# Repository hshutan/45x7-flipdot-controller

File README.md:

**This project is old! I do not recommend my hardware based project anymore, check out my RS-485 protocol-based projects! [Main Flipdot Project Page Here](https://github.com/hshutan/FlipDotCompendium)**

---

# 45x7-flipdot-controller
Custom PCB controller board for a single 45x7 flip dot panel from a Luminator MAX3000 SideSign

# How To

**A much more [detailed How To](#detailed) is below**

You will need the following items to assemble a flip dot sign using my PCB

1. The PCB in this github project which can be ordered from [OSH Park](https://oshpark.com/shared_projects/JROcn5LK) or another fab.
2. [My simple Arduino clock program](https://github.com/hshutan/FlipDotDisplay_Clock1_SWv1) which contains my `Matrix_CoProcessor` library, a library specifically built to drive this PCB.
3. Surface mount silicon parts: see the [Digi-Key BOM file](https://github.com/hshutan/45x7-flipdot-controller/blob/master/FlipDotBOM.csv)
  - Note that the Digi-Key BOM does not include the two through hole capacitors you will need.
4. A Luminator MAX3000 Side Sign.
  - I purchased mine from [Rollsign Gallery](http://rollsigngallery.com/). A single Luminator MAX3000 side sign will have two 45x7 display panels inside, which are very easy to remove.
5. A microcontroller or Arduino, and various power supply components to provide the different needed voltages.
  - I like Paul Stoffregen's Arduino compatible [Teensy](http://www.pjrc.com/) but often use [Arduino Pro Mini](https://www.arduino.cc/en/Main/ArduinoBoardProMini) clones from eBay for less demanding projects.

# Notes
The silkscreen for the 64 pin connector is for aesthetics. You should install the connector on the back of the board not the front, using the silkscreen for orientation reference only.

There are three voltages: Logic (5v), Flip (12-15v), LED (19v or 400mA max)

HW Rev1 of the PCB does not include any current limiting for the flip dots, or for the LEDs. I am using a 60mA current limiter in-line with the flip dot voltage line. The dots seem to flip best based on voltage and not current, which is why I am using such a small current. The LEDs are meant to be driven at 19 volts max, however less is safer. A current limit of 350mA would be safe for the LEDs.

My first prototype clock/sign with this PCB uses 15 volts for both the LEDs and flip dots. This means the LEDs are always on, although not near their maximum brightness. I am using a 5 volt Arduino Pro Mini, and also supplying 5 volts to the logic voltage input on the PCB.

Watch for ground loops, as I believe these cause weak/un-reliable flips. Because the grounds are all "commoned" on the PCB, do not tie any of your grounds together pre-PCB.

Luminator and MAX3000 are trade names of the Luminator Technology Group, not mine.

# Detailed How To / Step by Step Instructions
1. Acquire a Luminator MAX3000 Side Sign. I found mine on [Rollsign Gallery](http://rollsigngallery.com/).
  - A single Luminator side sign will contain two 45x7 panels.
2. Order the PCB in this github project, it can be ordered with a few clicks from [OSH Park](https://oshpark.com/shared_projects/JROcn5LK)
3. Order the bill of materials ([see CSV file](https://github.com/hshutan/45x7-flipdot-controller/blob/master/FlipDotBOM.csv))
  - Also grab two spare through hole capacitors from your parts bin. Try a 50 volt 330 microfarad for the flip voltage, and a 16 volt 100 microfarad capacitor for the logic voltage.
4. Take apart the MAX3000 side sign and remove both of the 45x7 panels.
5. Assemble the PCB by placing all components and soldering. Hot air can be used for all the surface mount components.
  - For aesthetics, the PCB has very little silk screen. Here is how to place components: Pin 1 of each IC is in the lower left of the land pattern when viewing the board from the top (see PCB pictures at the top of this page).
  - The 0805 (2012 Metric) pads in the lower right area of the PCB are for the pull-up and pull-down resistors.
  - The 0805 (2012 Metric) pads in the upper left of the PCB are for the 0.1 microfarad shift register supporting capacitors.
6. Program an Arduino or microcontroller with the [test pattern](https://github.com/hshutan/FlipDotDisplay_TestPatterns_SWv1) software. A good test pattern to start with is `testPattern2()`
7. Hook up the Arduino per the comments in the code:
  - Arduino Uno pin 11, to SER on PCB
  - Arduino Uno pin 13, to SCK on PCB
  - Arduino Uno pin 10, to RCK on PCB
  - Arduino 5v, to 5v+ on PCB
8. Connect a power supply (start with 10-12 volts) to GND and Flip+ on the PCB.
  - For prototyping, use a constant voltage/constant current power supply. This will allow you to limit the current to 100mA (or less) for safety, and also to test flip reliability at different voltages. If you are using my `Matrix_CoProcessor` library that comes with the [test pattern](https://github.com/hshutan/FlipDotDisplay_TestPatterns_SWv1) software, then there is little risk of a flip dot being energized for more than a few hundred microseconds, however you should still use current limiting of 100mA or less to prevent damage if any paths remain energized for too long.

# Thanks
I would like to thank the following sources:
- [Dottie the Flip Dot Clock](http://dhenshaw.com/Art/Dottie/start.html)
- [Rollsign Gallery](http://rollsigngallery.com/)

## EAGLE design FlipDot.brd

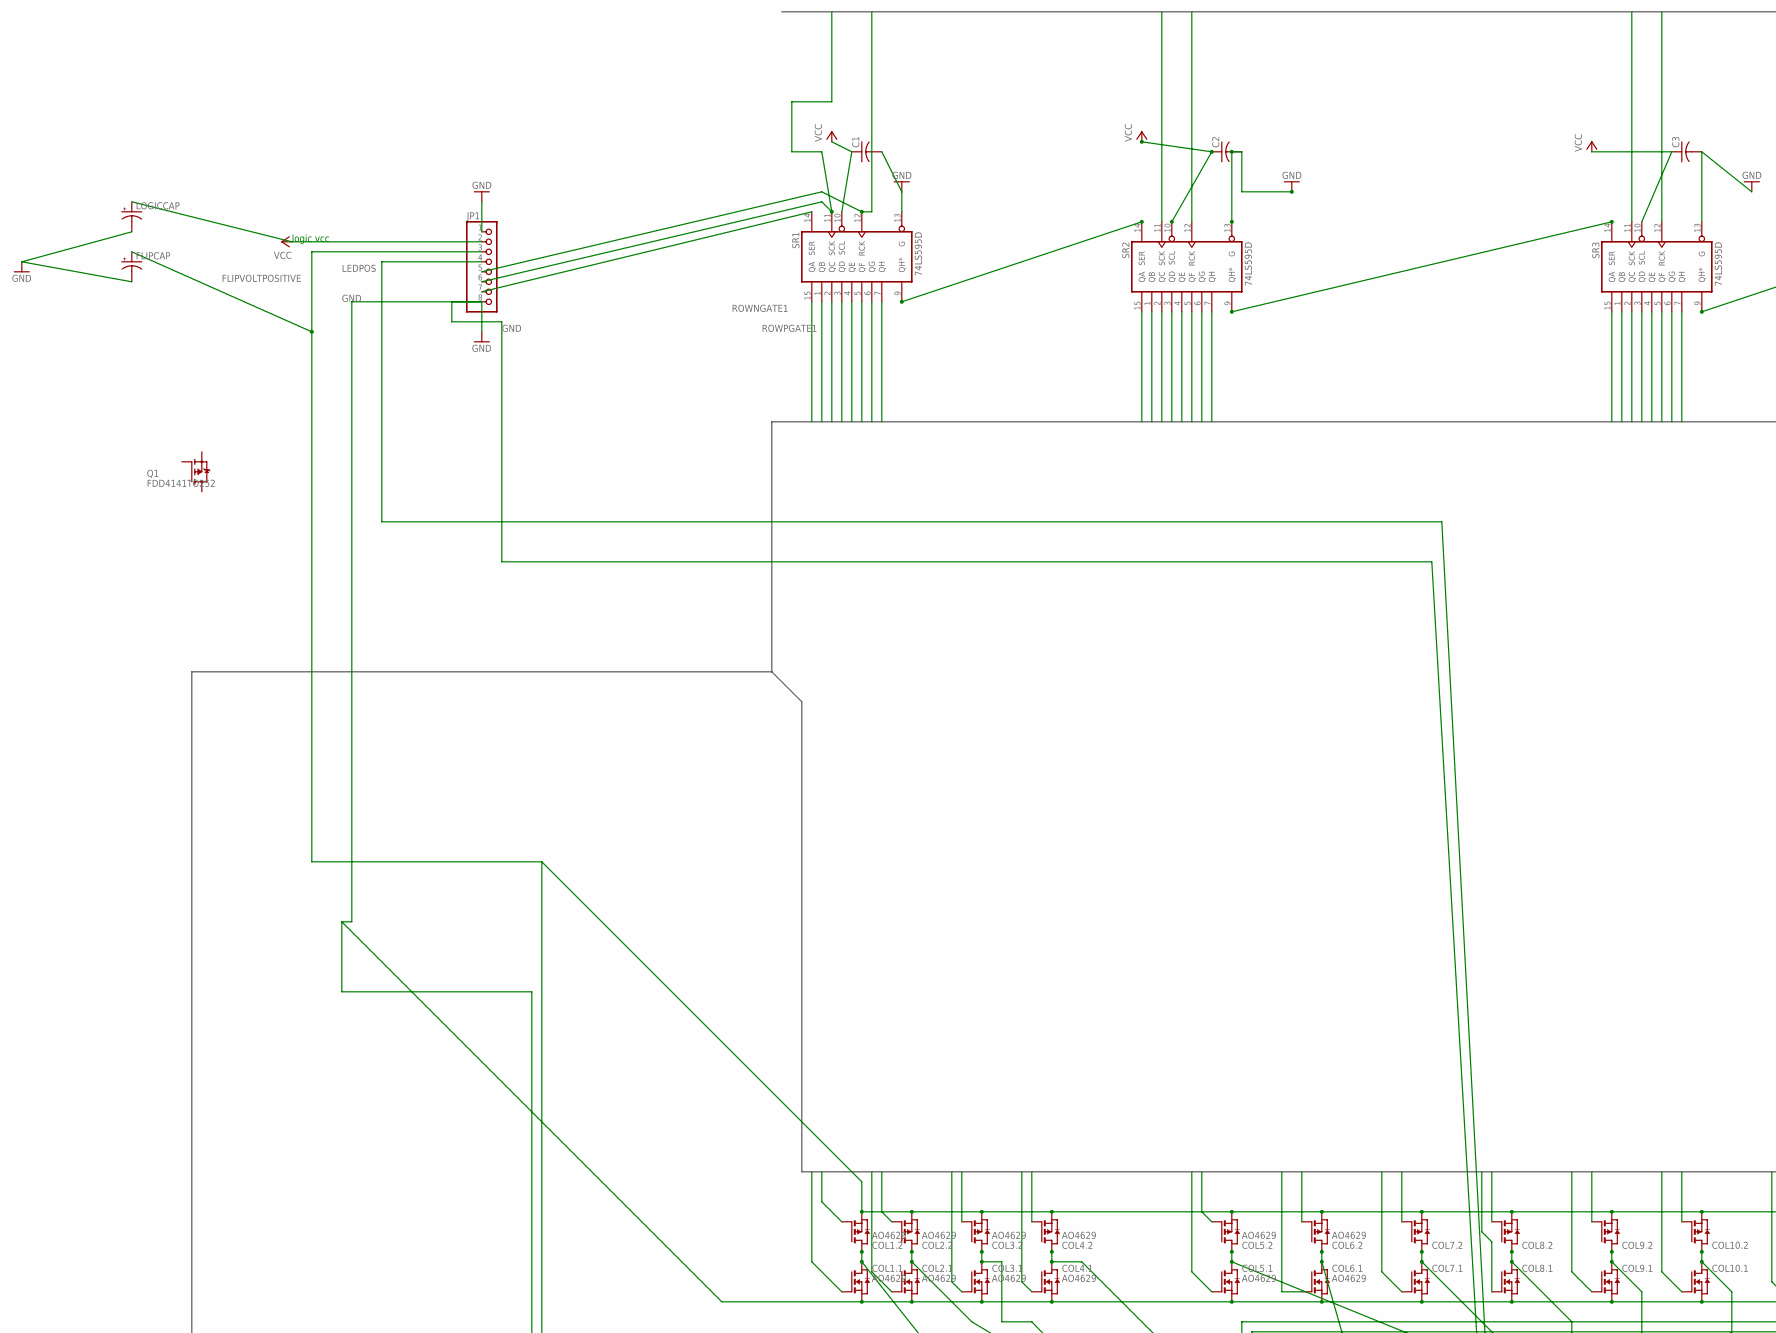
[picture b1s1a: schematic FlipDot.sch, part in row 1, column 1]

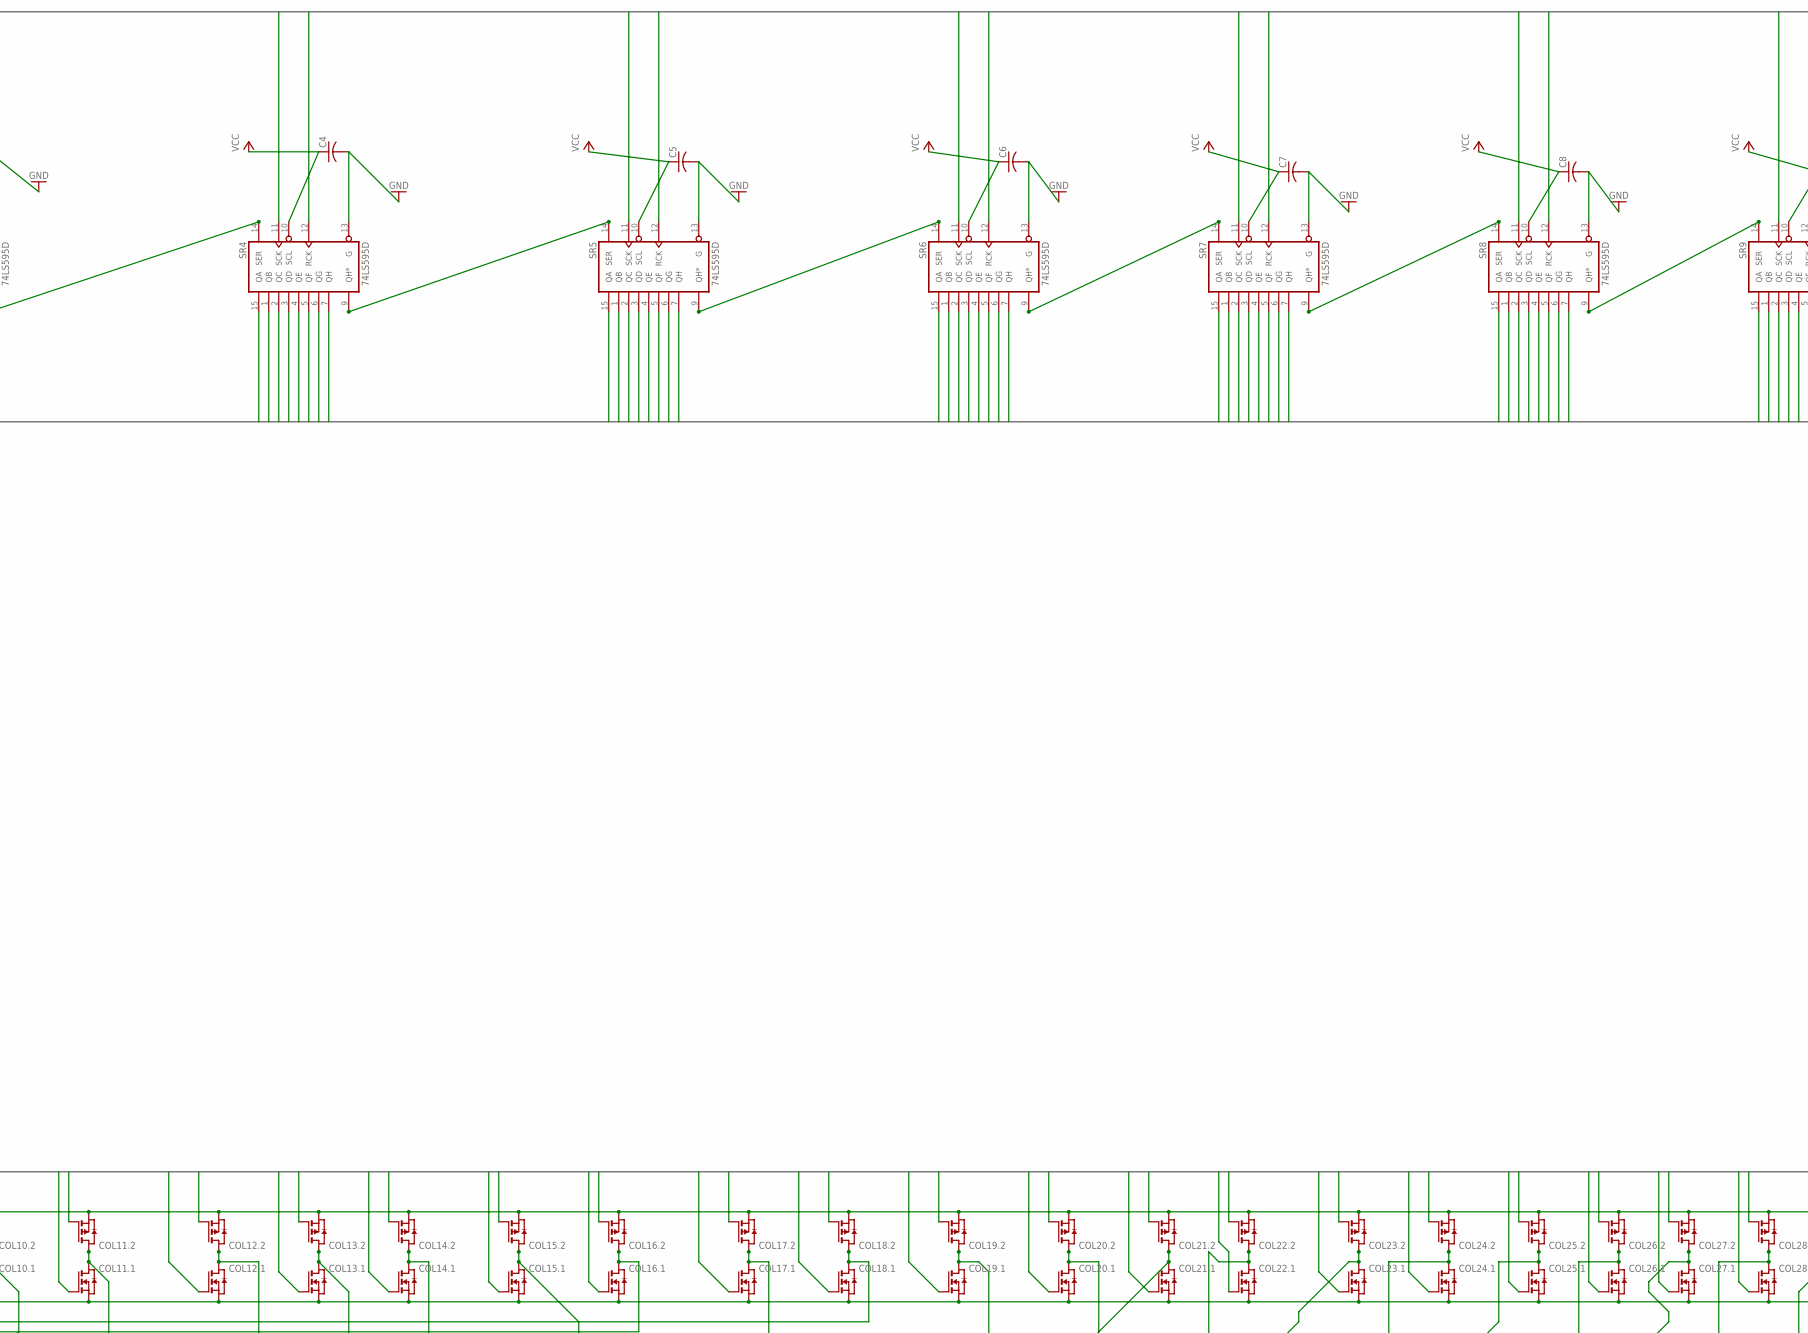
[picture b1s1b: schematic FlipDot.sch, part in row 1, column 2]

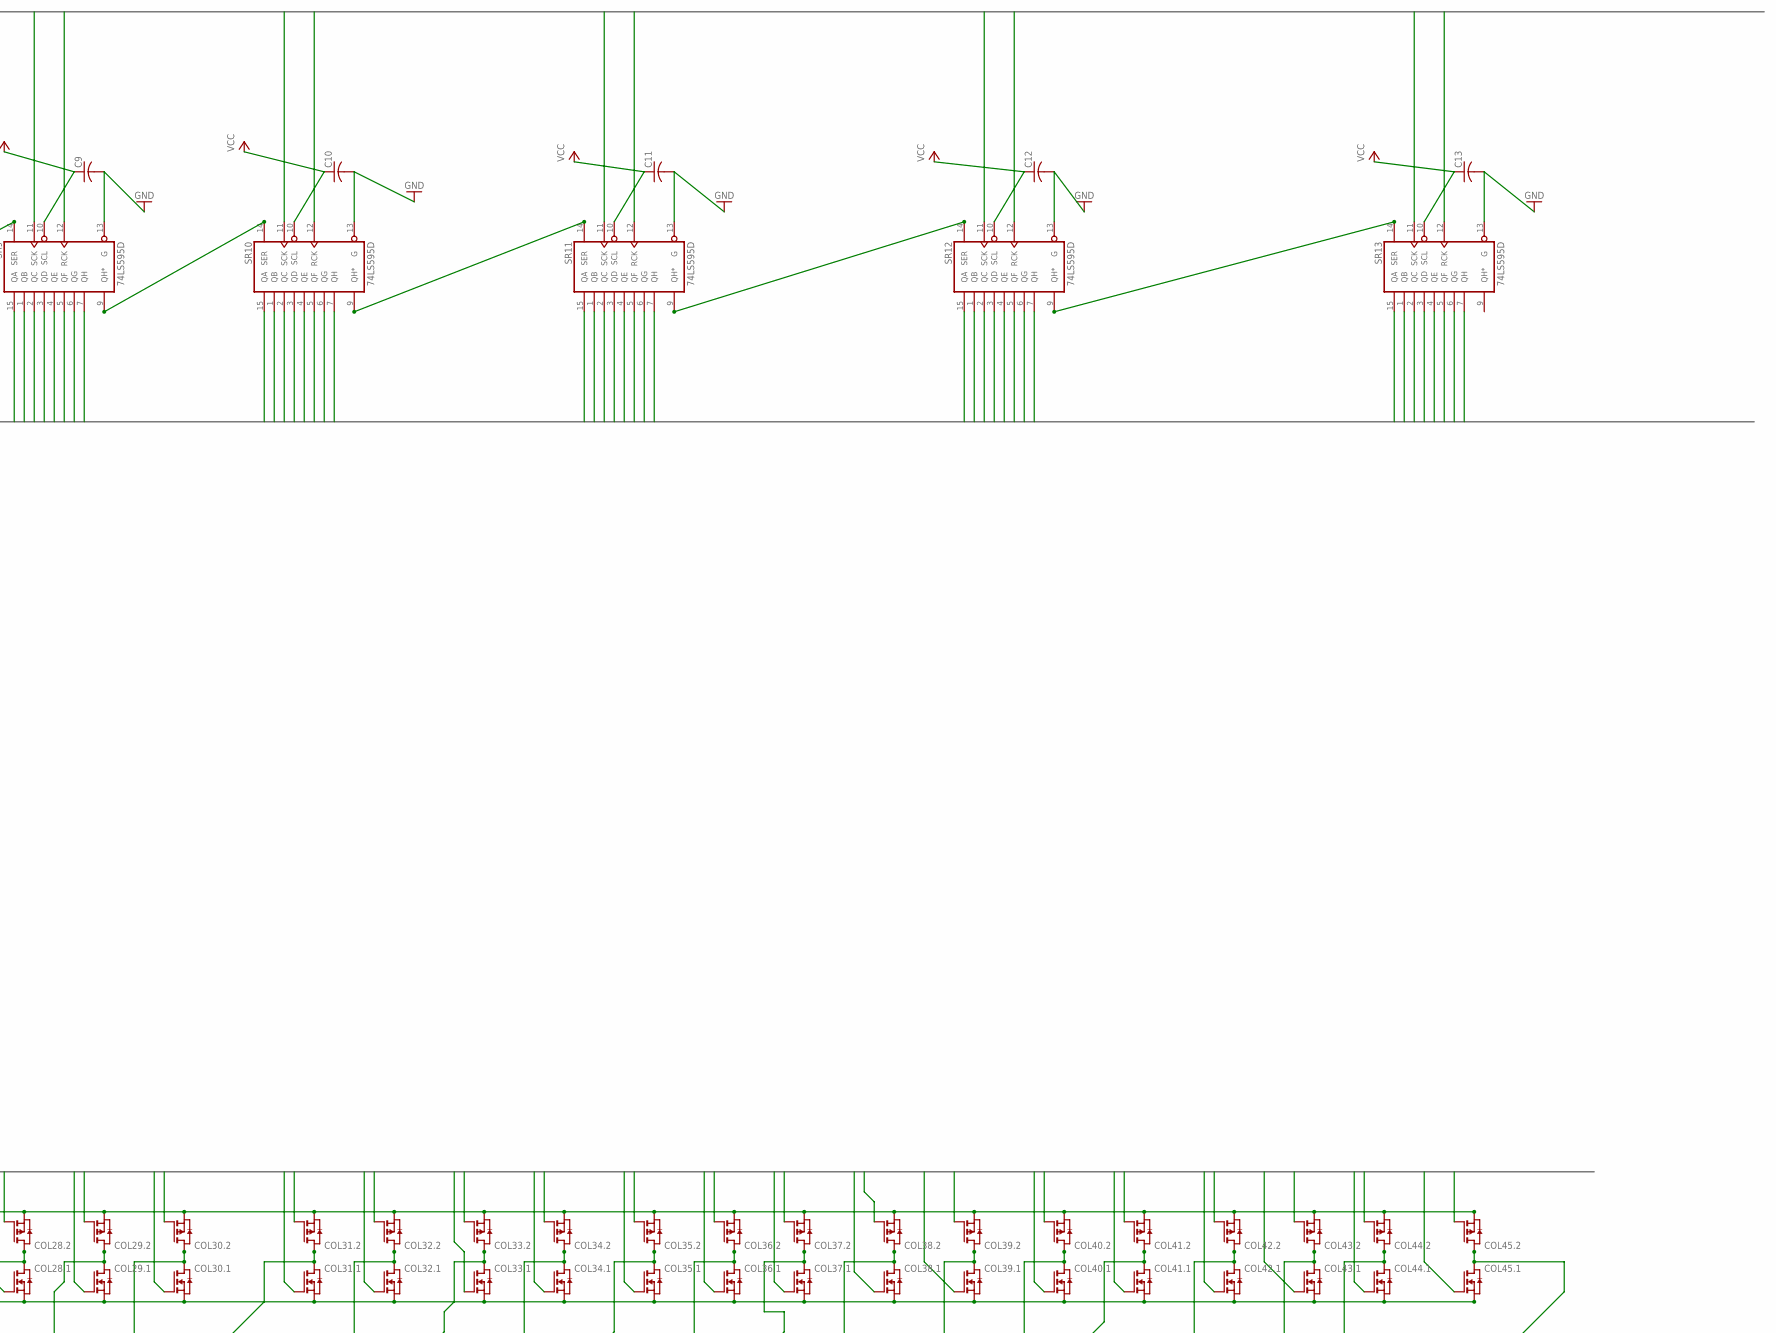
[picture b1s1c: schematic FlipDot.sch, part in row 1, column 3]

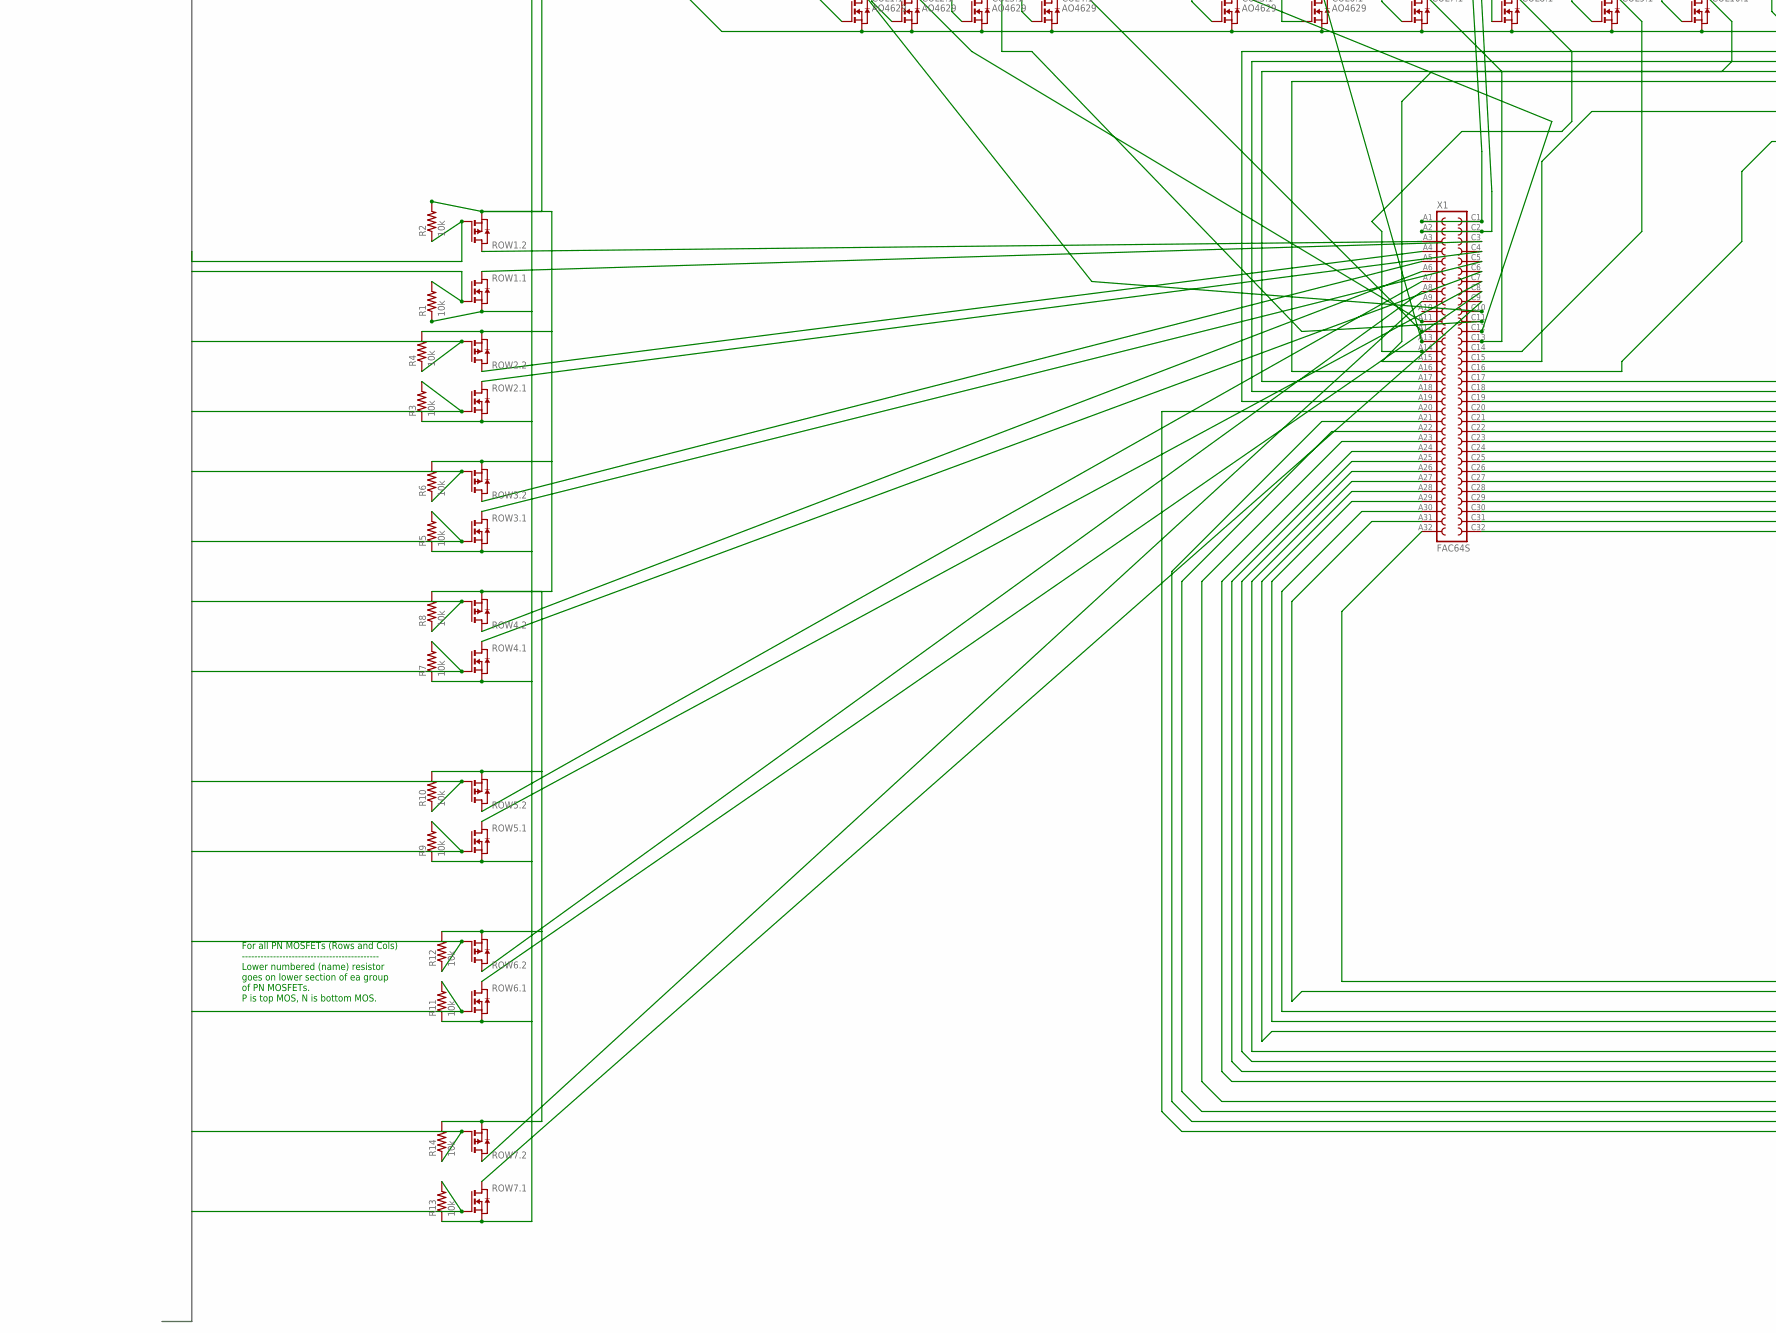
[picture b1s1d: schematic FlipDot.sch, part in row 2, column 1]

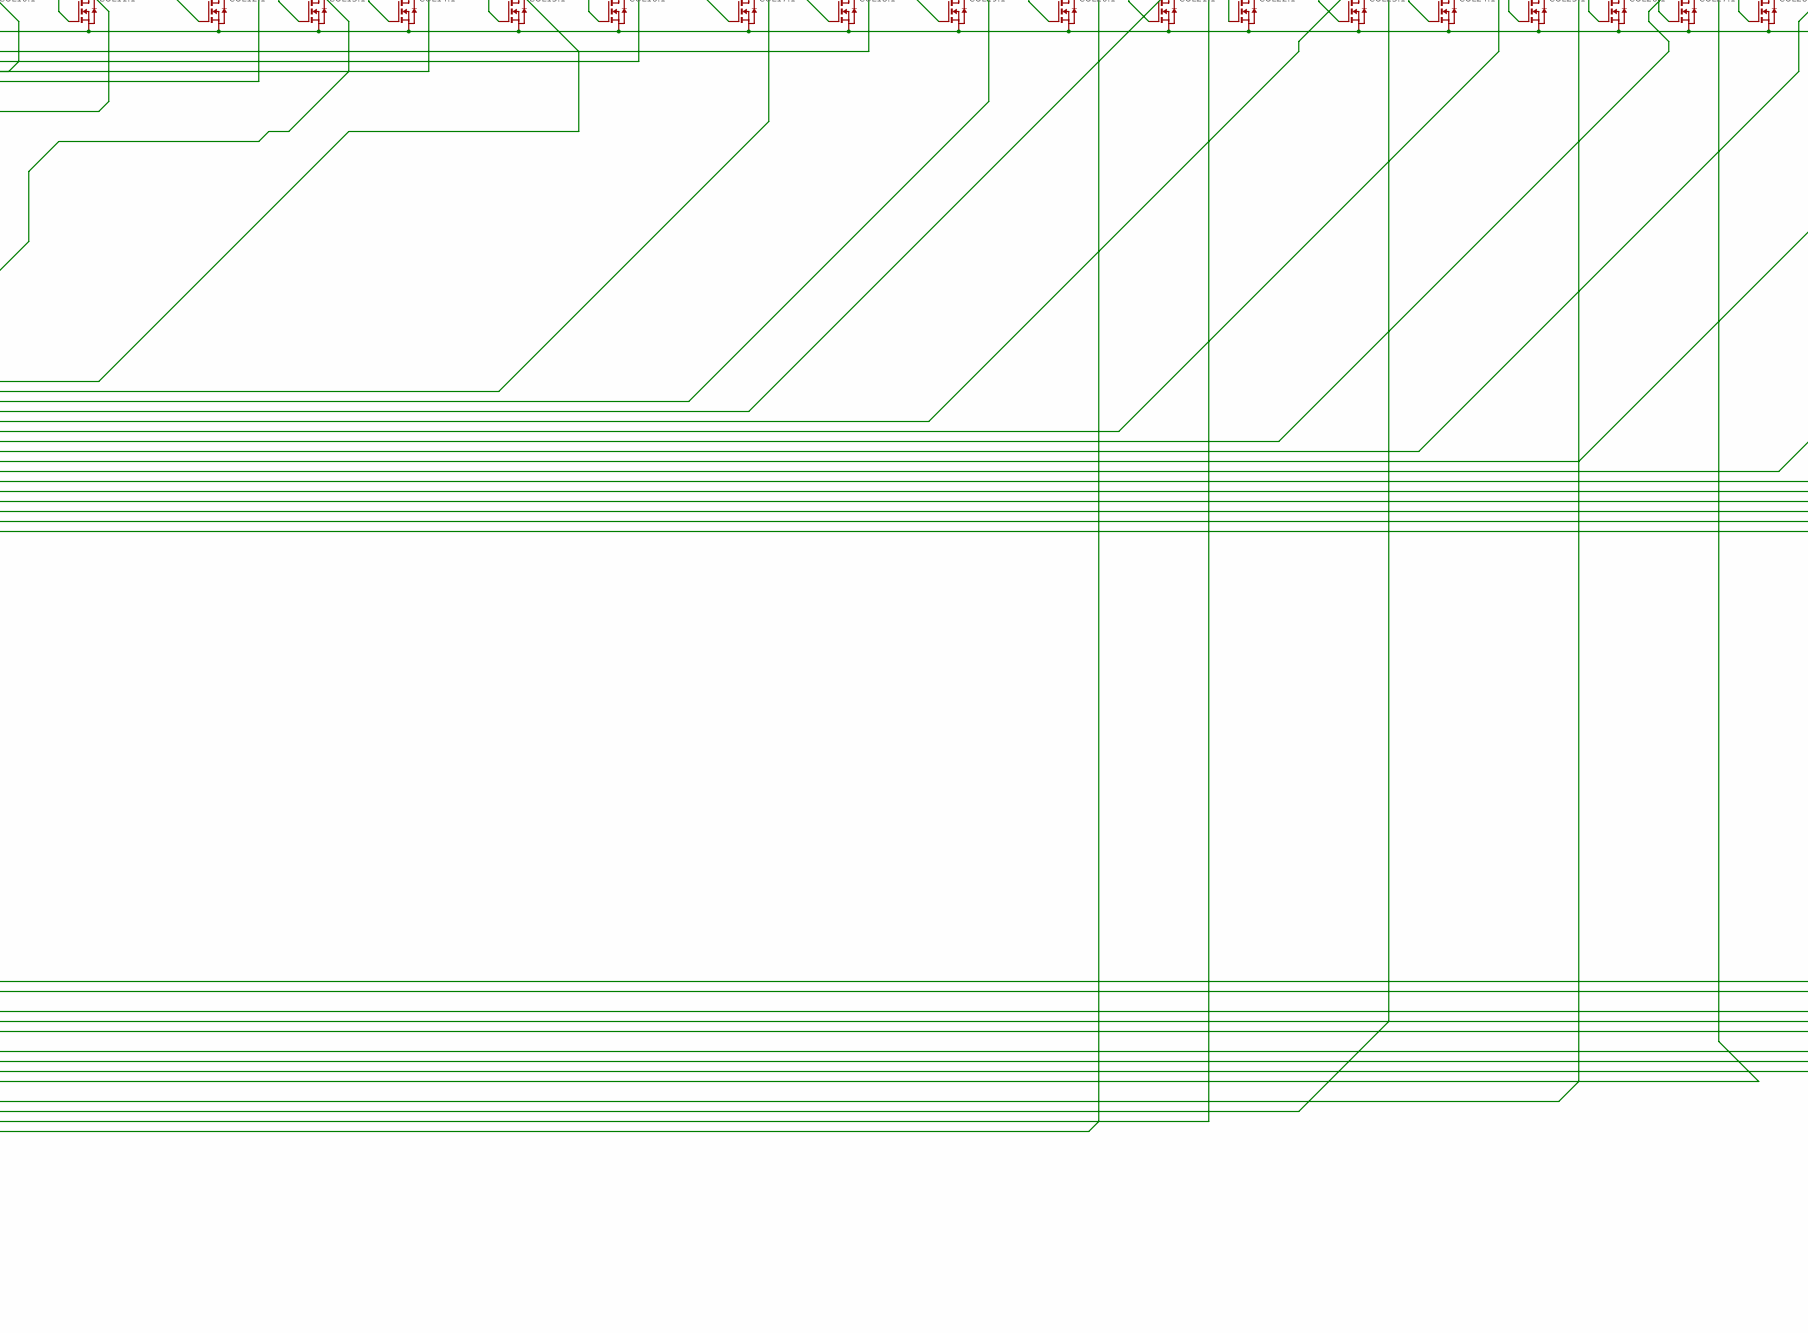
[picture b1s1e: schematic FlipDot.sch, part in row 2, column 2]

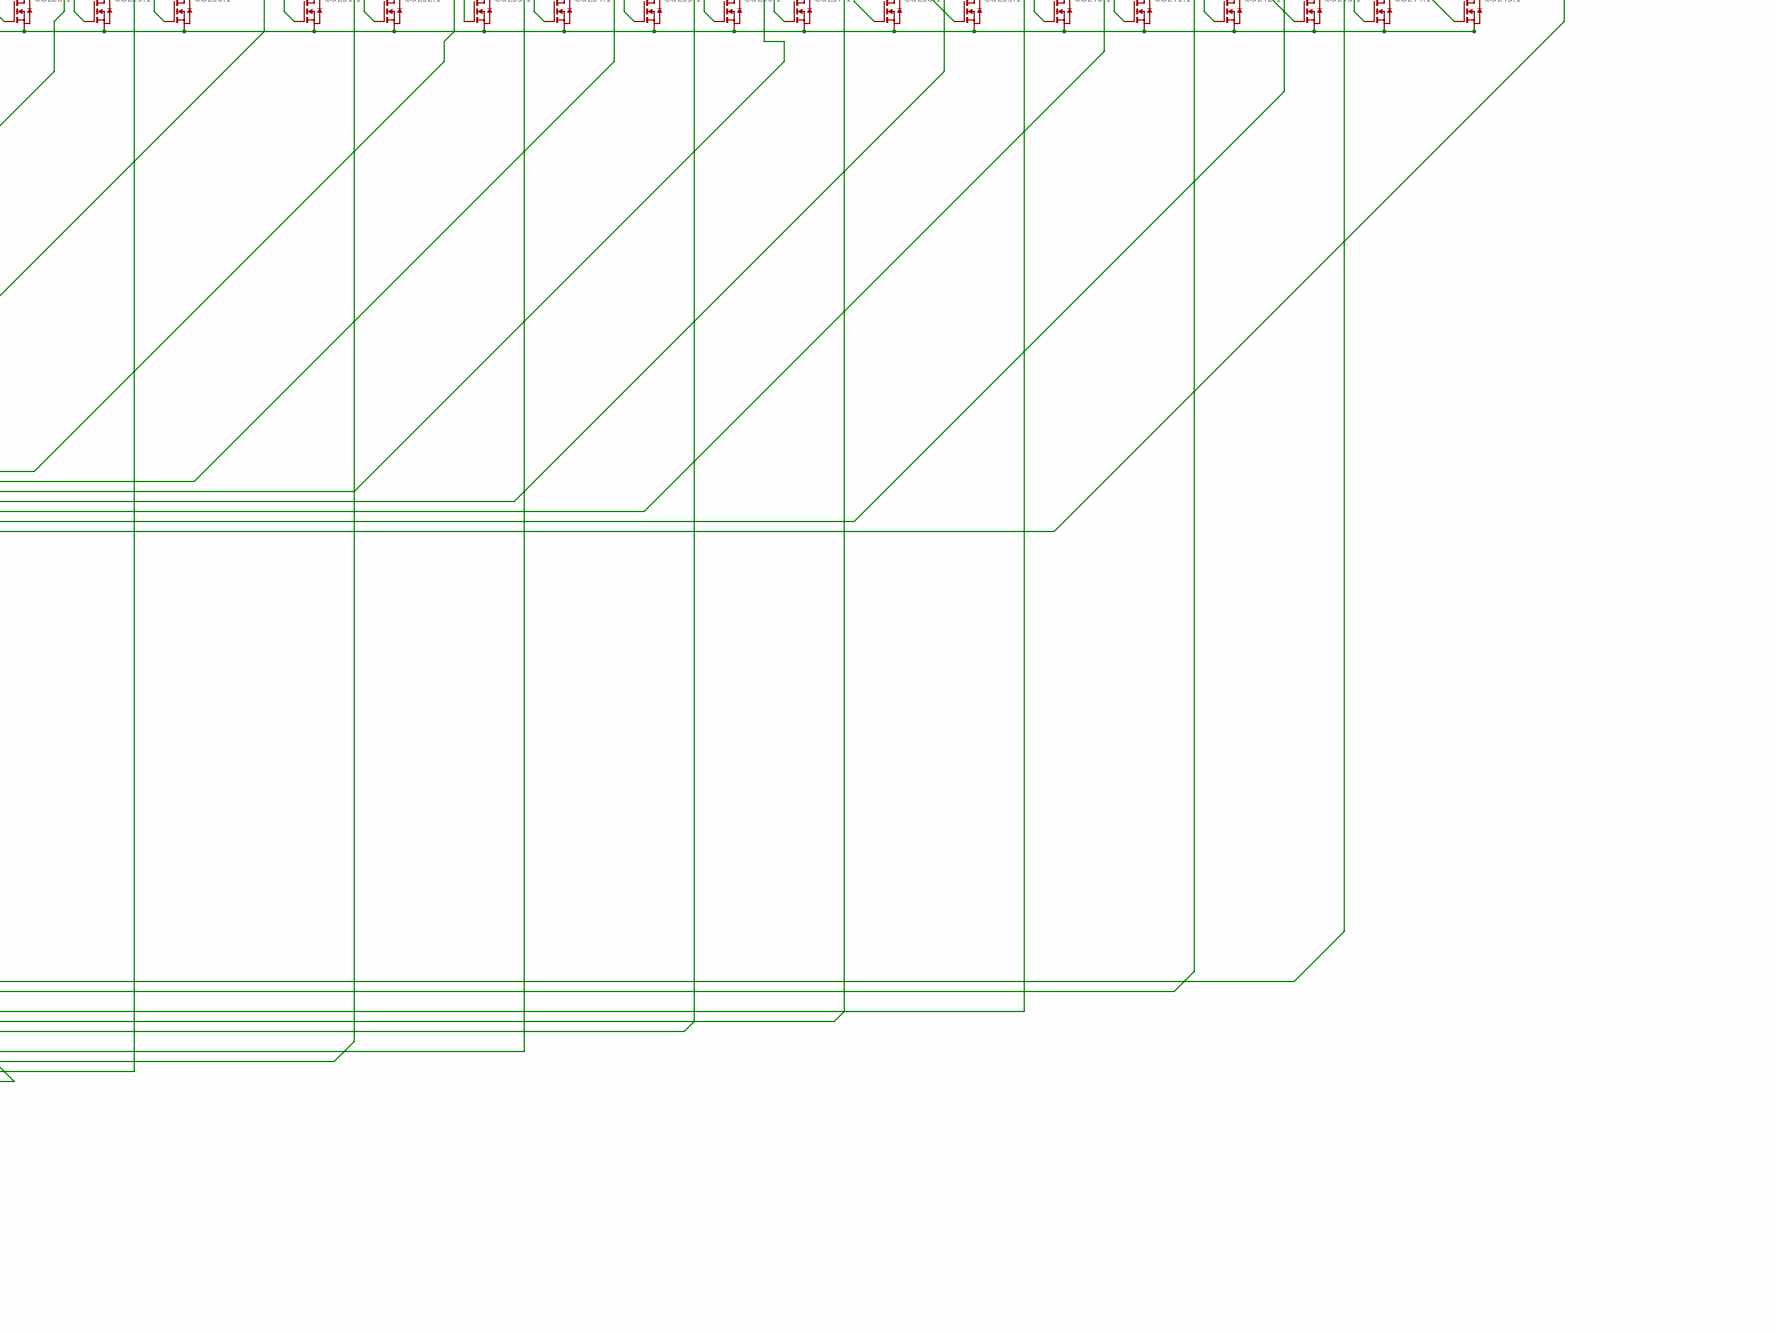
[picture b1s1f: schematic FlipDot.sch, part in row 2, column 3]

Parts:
C1, C2, C3, C4, C5, C6, C7, C8, C9, C10, C11, C12, C13: C-USC2012; C2012
COL1., COL2., COL3., COL4., COL5., COL6.: AO4629; SO8
COL7., COL8., COL9., COL10., COL11., COL12., COL13., COL14., COL15., COL16., COL17., COL18., COL19., COL20., COL21., COL22., COL23., COL24., COL25., COL26., COL27., COL28., COL29., COL30., COL31., COL32., COL33., COL34., COL35., COL36., COL37., COL38., COL39., COL40., COL41., COL42., COL43., COL44., COL45.: PN_MOSFET-SO8; SO8
FLIPCAP: CPOL-USE5-10.5; E5-10,5
JP1: PINHD-1X8; 1X08
LOGICCAP: CPOL-USE5-10.5; E5-10,5
Q1: FDD4141TO252; TO252
R1, R2, R3, R4, R5, R6, R7, R8, R9, R10, R11, R12, R13, R14: 10k; R2012
ROW1., ROW2., ROW3., ROW4., ROW5., ROW6., ROW7.: PN_MOSFET-SO8; SO8
SR1, SR2, SR3, SR4, SR5, SR6, SR7, SR8, SR9, SR10, SR11, SR12, SR13: 74LS595D; SO16
X1: FAC64S

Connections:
COL1COMMON: COL1..5 (D), COL1..6 (D), COL1..7 (D), COL1..8 (D), X1.C10
COL2COMMON: COL2..5 (D), COL2..6 (D), COL2..7 (D), COL2..8 (D), X1.A11
COL3COMMON: COL3..5 (D), COL3..6 (D), COL3..7 (D), COL3..8 (D), X1.C11
COL4COMMON: COL4..5 (D), COL4..6 (D), COL4..7 (D), COL4..8 (D), X1.A12
COL5COMMON: COL5..5 (D), COL5..6 (D), COL5..7 (D), COL5..8 (D), X1.C12
COL6COMMON: COL6..5 (D), COL6..6 (D), COL6..7 (D), COL6..8 (D), X1.A13
COL7COMMON: COL7..5 (D), COL7..6 (D), COL7..7 (D), COL7..8 (D), X1.C13
COL8COMMON: COL8..5 (D), COL8..6 (D), COL8..7 (D), COL8..8 (D), X1.A14
COL9COMMON: COL9..5 (D), COL9..6 (D), COL9..7 (D), COL9..8 (D), X1.C14
COL10COMMON: COL10..5 (D), COL10..6 (D), COL10..7 (D), COL10..8 (D), X1.A15
COL11COMMON: COL11..5 (D), COL11..6 (D), COL11..7 (D), COL11..8 (D), X1.C15
COL12COMMON: COL12..5 (D), COL12..6 (D), COL12..7 (D), COL12..8 (D), X1.A16
COL13COMMON: COL13..5 (D), COL13..6 (D), COL13..7 (D), COL13..8 (D), X1.C16
COL14COMMON: COL14..5 (D), COL14..6 (D), COL14..7 (D), COL14..8 (D), X1.A17
COL15COMMON: COL15..5 (D), COL15..6 (D), COL15..7 (D), COL15..8 (D), X1.C17
COL16COMMON: COL16..5 (D), COL16..6 (D), COL16..7 (D), COL16..8 (D), X1.A18
COL17COMMON: COL17..5 (D), COL17..6 (D), COL17..7 (D), COL17..8 (D), X1.C18
COL18COMMON: COL18..5 (D), COL18..6 (D), COL18..7 (D), COL18..8 (D), X1.A19
COL19COMMON: COL19..5 (D), COL19..6 (D), COL19..7 (D), COL19..8 (D), X1.C19
COL20COMMON: COL20..5 (D), COL20..6 (D), COL20..7 (D), COL20..8 (D), X1.A20
COL21COMMON: COL21..5 (D), COL21..6 (D), COL21..7 (D), COL21..8 (D), X1.C20
COL22COMMON: COL22..5 (D), COL22..6 (D), COL22..7 (D), COL22..8 (D), X1.A21
COL23COMMON: COL23..5 (D), COL23..6 (D), COL23..7 (D), COL23..8 (D), X1.C21
COL24COMMON: COL24..5 (D), COL24..6 (D), COL24..7 (D), COL24..8 (D), X1.A22
COL25COMMON: COL25..5 (D), COL25..6 (D), COL25..7 (D), COL25..8 (D), X1.C22
COL26COMMON: COL26..5 (D), COL26..6 (D), COL26..7 (D), COL26..8 (D), X1.A23
COL27COMMON: COL27..5 (D), COL27..6 (D), COL27..7 (D), COL27..8 (D), X1.C23
COL28COMMON: COL28..5 (D), COL28..6 (D), COL28..7 (D), COL28..8 (D), X1.A24
COL29COMMON: COL29..5 (D), COL29..6 (D), COL29..7 (D), COL29..8 (D), X1.C24
COL30COMMON: COL30..5 (D), COL30..6 (D), COL30..7 (D), COL30..8 (D), X1.A25
COL31COMMON: COL31..5 (D), COL31..6 (D), COL31..7 (D), COL31..8 (D), X1.C25
COL32COMMON: COL32..5 (D), COL32..6 (D), COL32..7 (D), COL32..8 (D), X1.A26
COL33COMMON: COL33..5 (D), COL33..6 (D), COL33..7 (D), COL33..8 (D), X1.C26
COL34COMMON: COL34..5 (D), COL34..6 (D), COL34..7 (D), COL34..8 (D), X1.A27
COL35COMMON: COL35..5 (D), COL35..6 (D), COL35..7 (D), COL35..8 (D), X1.C27
COL36COMMON: COL36..5 (D), COL36..6 (D), COL36..7 (D), COL36..8 (D), X1.A28
COL37COMMON: COL37..5 (D), COL37..6 (D), COL37..7 (D), COL37..8 (D), X1.C28
COL38COMMON: COL38..5 (D), COL38..6 (D), COL38..7 (D), COL38..8 (D), X1.A29
COL39COMMON: COL39..5 (D), COL39..6 (D), COL39..7 (D), COL39..8 (D), X1.C29
COL40COMMON: COL40..5 (D), COL40..6 (D), COL40..7 (D), COL40..8 (D), X1.A30
COL41COMMON: COL41..5 (D), COL41..6 (D), COL41..7 (D), COL41..8 (D), X1.C30
COL42COMMON: COL42..5 (D), COL42..6 (D), COL42..7 (D), COL42..8 (D), X1.A31
COL43COMMON: COL43..5 (D), COL43..6 (D), COL43..7 (D), COL43..8 (D), X1.C31
COL44COMMON: COL44..5 (D), COL44..6 (D), COL44..7 (D), COL44..8 (D), X1.A32
COL45COMMON: COL45..5 (D), COL45..6 (D), COL45..7 (D), COL45..8 (D), X1.C32
COLNGATE1: COL1..2 (G), SR2.6 (QG)
COLNGATE2: COL2..2 (G), SR3.15 (QA)
COLNGATE3: COL3..2 (G), SR3.2 (QC)
COLNGATE4: COL4..2 (G), SR3.4 (QE)
COLNGATE5: COL5..2 (G), SR3.6 (QG)
COLNGATE6: COL6..2 (G), SR4.15 (QA)
COLNGATE7: COL7..2 (G), SR4.2 (QC)
COLNGATE8: COL8..2 (G), SR4.4 (QE)
COLNGATE9: COL9..2 (G), SR4.6 (QG)
COLNGATE10: COL10..2 (G), SR5.15 (QA)
COLNGATE11: COL11..2 (G), SR5.2 (QC)
COLNGATE12: COL12..2 (G), SR5.4 (QE)
COLNGATE13: COL13..2 (G), SR5.6 (QG)
COLNGATE14: COL14..2 (G), SR6.15 (QA)
COLNGATE15: COL15..2 (G), SR6.2 (QC)
COLNGATE16: COL16..2 (G), SR6.4 (QE)
COLNGATE17: COL17..2 (G), SR6.6 (QG)
COLNGATE18: COL18..2 (G), SR7.15 (QA)
COLNGATE19: COL19..2 (G), SR7.2 (QC)
COLNGATE20: COL20..2 (G), SR7.4 (QE)
COLNGATE21: COL21..2 (G), SR7.6 (QG)
COLNGATE22: COL22..2 (G), SR8.15 (QA)
COLNGATE23: COL23..2 (G), SR8.2 (QC)
COLNGATE24: COL24..2 (G), SR8.4 (QE)
COLNGATE25: COL25..2 (G), SR8.6 (QG)
COLNGATE26: COL26..2 (G), SR9.15 (QA)
COLNGATE27: COL27..2 (G), SR9.2 (QC)
COLNGATE28: COL28..2 (G), SR9.4 (QE)
COLNGATE29: COL29..2 (G), SR9.6 (QG)
COLNGATE30: COL30..2 (G), SR10.15 (QA)
COLNGATE31: COL31..2 (G), SR10.2 (QC)
COLNGATE32: COL32..2 (G), SR10.4 (QE)
COLNGATE33: COL33..2 (G), SR10.6 (QG)
COLNGATE34: COL34..2 (G), SR11.15 (QA)
COLNGATE35: COL35..2 (G), SR11.2 (QC)
COLNGATE36: COL36..2 (G), SR11.4 (QE)
COLNGATE37: COL37..2 (G), SR11.6 (QG)
COLNGATE38: COL38..2 (G), SR12.15 (QA)
COLNGATE39: COL39..2 (G), SR12.2 (QC)
COLNGATE40: COL40..2 (G), SR12.4 (QE)
COLNGATE41: COL41..2 (G), SR12.6 (QG)
COLNGATE42: COL42..2 (G), SR13.15 (QA)
COLNGATE43: COL43..2 (G), SR13.2 (QC)
COLNGATE44: COL44..2 (G), SR13.4 (QE)
COLNGATE45: COL45..2 (G), SR13.6 (QG)
COLPGATE1: COL1..4 (G), SR2.7 (QH)
COLPGATE2: COL2..4 (G), SR3.1 (QB)
COLPGATE3: COL3..4 (G), SR3.3 (QD)
COLPGATE4: COL4..4 (G), SR3.5 (QF)
COLPGATE5: COL5..4 (G), SR3.7 (QH)
COLPGATE6: COL6..4 (G), SR4.1 (QB)
COLPGATE7: COL7..4 (G), SR4.3 (QD)
COLPGATE8: COL8..4 (G), SR4.5 (QF)
COLPGATE9: COL9..4 (G), SR4.7 (QH)
COLPGATE10: COL10..4 (G), SR5.1 (QB)
COLPGATE11: COL11..4 (G), SR5.3 (QD)
COLPGATE12: COL12..4 (G), SR5.5 (QF)
COLPGATE13: COL13..4 (G), SR5.7 (QH)
COLPGATE14: COL14..4 (G), SR6.1 (QB)
COLPGATE15: COL15..4 (G), SR6.3 (QD)
COLPGATE16: COL16..4 (G), SR6.5 (QF)
COLPGATE17: COL17..4 (G), SR6.7 (QH)
COLPGATE18: COL18..4 (G), SR7.1 (QB)
COLPGATE19: COL19..4 (G), SR7.3 (QD)
COLPGATE20: COL20..4 (G), SR7.5 (QF)
COLPGATE21: COL21..4 (G), SR7.7 (QH)
COLPGATE22: COL22..4 (G), SR8.1 (QB)
COLPGATE23: COL23..4 (G), SR8.3 (QD)
COLPGATE24: COL24..4 (G), SR8.5 (QF)
COLPGATE25: COL25..4 (G), SR8.7 (QH)
COLPGATE26: COL26..4 (G), SR9.1 (QB)
COLPGATE27: COL27..4 (G), SR9.3 (QD)
COLPGATE28: COL28..4 (G), SR9.5 (QF)
COLPGATE29: COL29..4 (G), SR9.7 (QH)
COLPGATE30: COL30..4 (G), SR10.1 (QB)
COLPGATE31: COL31..4 (G), SR10.3 (QD)
COLPGATE32: COL32..4 (G), SR10.5 (QF)
COLPGATE33: COL33..4 (G), SR10.7 (QH)
COLPGATE34: COL34..4 (G), SR11.1 (QB)
COLPGATE35: COL35..4 (G), SR11.3 (QD)
COLPGATE36: COL36..4 (G), SR11.5 (QF)
COLPGATE37: COL37..4 (G), SR11.7 (QH)
COLPGATE38: COL38..4 (G), SR12.1 (QB)
COLPGATE39: COL39..4 (G), SR12.3 (QD)
COLPGATE40: COL40..4 (G), SR12.5 (QF)
COLPGATE41: COL41..4 (G), SR12.7 (QH)
COLPGATE42: COL42..4 (G), SR13.1 (QB)
COLPGATE43: COL43..4 (G), SR13.3 (QD)
COLPGATE44: COL44..4 (G), SR13.5 (QF)
COLPGATE45: COL45..4 (G), SR13.7 (QH)
FLIPVOLTPOSITIVE: COL1..3 (S), COL2..3 (S), COL3..3 (S), COL4..3 (S), COL5..3 (S), COL6..3 (S), COL7..3 (S), COL8..3 (S), COL9..3 (S), COL10..3 (S), COL11..3 (S), COL12..3 (S), COL13..3 (S), COL14..3 (S), COL15..3 (S), COL16..3 (S), COL17..3 (S), COL18..3 (S), COL19..3 (S), COL20..3 (S), COL21..3 (S), COL22..3 (S), COL23..3 (S), COL24..3 (S), COL25..3 (S), COL26..3 (S), COL27..3 (S), COL28..3 (S), COL29..3 (S), COL30..3 (S), COL31..3 (S), COL32..3 (S), COL33..3 (S), COL34..3 (S), COL35..3 (S), COL36..3 (S), COL37..3 (S), COL38..3 (S), COL39..3 (S), COL40..3 (S), COL41..3 (S), COL42..3 (S), COL43..3 (S), COL44..3 (S), COL45..3 (S), FLIPCAP.+, JP1.3, R2.2, R4.2, R6.2, R8.2, R10.2, R12.2, R14.2, ROW1..3 (S), ROW2..3 (S), ROW3..3 (S), ROW4..3 (S), ROW5..3 (S), ROW6..3 (S), ROW7..3 (S)
GND: C1.2, C2.2, C3.2, C4.2, C5.2, C6.2, C7.2, C8.2, C9.2, C10.2, C11.2, C12.2, C13.2, COL1..1 (S), COL2..1 (S), COL3..1 (S), COL4..1 (S), COL5..1 (S), COL6..1 (S), COL7..1 (S), COL8..1 (S), COL9..1 (S), COL10..1 (S), COL11..1 (S), COL12..1 (S), COL13..1 (S), COL14..1 (S), COL15..1 (S), COL16..1 (S), COL17..1 (S), COL18..1 (S), COL19..1 (S), COL20..1 (S), COL21..1 (S), COL22..1 (S), COL23..1 (S), COL24..1 (S), COL25..1 (S), COL26..1 (S), COL27..1 (S), COL28..1 (S), COL29..1 (S), COL30..1 (S), COL31..1 (S), COL32..1 (S), COL33..1 (S), COL34..1 (S), COL35..1 (S), COL36..1 (S), COL37..1 (S), COL38..1 (S), COL39..1 (S), COL40..1 (S), COL41..1 (S), COL42..1 (S), COL43..1 (S), COL44..1 (S), COL45..1 (S), FLIPCAP.-, JP1.1, JP1.8, LOGICCAP.-, R1.1, R3.1, R5.1, R7.1, R9.1, R11.1, R13.1, ROW1..1 (S), ROW2..1 (S), ROW3..1 (S), ROW4..1 (S), ROW5..1 (S), ROW6..1 (S), ROW7..1 (S), SR1.8 (GND), SR1.13 (G), SR2.8 (GND), SR2.13 (G), SR3.8 (GND), SR3.13 (G), SR4.8 (GND), SR4.13 (G), SR5.8 (GND), SR5.13 (G), SR6.8 (GND), SR6.13 (G), SR7.8 (GND), SR7.13 (G), SR8.8 (GND), SR8.13 (G), SR9.8 (GND), SR9.13 (G), SR10.8 (GND), SR10.13 (G), SR11.8 (GND), SR11.13 (G), SR12.8 (GND), SR12.13 (G), SR13.8 (GND), SR13.13 (G), X1.A1, X1.C1
LEDPOS: JP1.4, X1.A2, X1.C2
MAINSERIALLINE: JP1.7, SR1.14 (SER)
RCK: JP1.5, SR1.12 (RCK), SR2.12 (RCK), SR3.12 (RCK), SR4.12 (RCK), SR5.12 (RCK), SR6.12 (RCK), SR7.12 (RCK), SR8.12 (RCK), SR9.12 (RCK), SR10.12 (RCK), SR11.12 (RCK), SR12.12 (RCK), SR13.12 (RCK)
ROW1NCOM: ROW1..7 (D), ROW1..8 (D), X1.C3
ROW1PCOM: ROW1..5 (D), ROW1..6 (D), X1.A3
ROW2NCOM: ROW2..7 (D), ROW2..8 (D), X1.C4
ROW2PCOM: ROW2..5 (D), ROW2..6 (D), X1.A4
ROW3NCOM: ROW3..7 (D), ROW3..8 (D), X1.C5
ROW3PCOM: ROW3..5 (D), ROW3..6 (D), X1.A5
ROW4NCOM: ROW4..7 (D), ROW4..8 (D), X1.C6
ROW4PCOM: ROW4..5 (D), ROW4..6 (D), X1.A6
ROW5NCOM: ROW5..7 (D), ROW5..8 (D), X1.C7
ROW5PCOM: ROW5..5 (D), ROW5..6 (D), X1.A7
ROW6NCOM: ROW6..7 (D), ROW6..8 (D), X1.C8
ROW6PCOM: ROW6..5 (D), ROW6..6 (D), X1.A8
ROW7NCOM: ROW7..7 (D), ROW7..8 (D), X1.C9
ROW7PCOM: ROW7..5 (D), ROW7..6 (D), X1.A9
ROWNGATE1: R1.2, ROW1..2 (G), SR1.15 (QA)
ROWNGATE2: R3.2, ROW2..2 (G), SR1.2 (QC)
ROWNGATE3: R5.2, ROW3..2 (G), SR1.4 (QE)
ROWNGATE4: R7.2, ROW4..2 (G), SR1.6 (QG)
ROWNGATE5: R9.2, ROW5..2 (G), SR2.15 (QA)
ROWNGATE6: R11.2, ROW6..2 (G), SR2.2 (QC)
ROWNGATE7: R13.2, ROW7..2 (G), SR2.4 (QE)
ROWPGATE1: R2.1, ROW1..4 (G), SR1.1 (QB)
ROWPGATE2: R4.1, ROW2..4 (G), SR1.3 (QD)
ROWPGATE3: R6.1, ROW3..4 (G), SR1.5 (QF)
ROWPGATE4: R8.1, ROW4..4 (G), SR1.7 (QH)
ROWPGATE5: R10.1, ROW5..4 (G), SR2.1 (QB)
ROWPGATE6: R12.1, ROW6..4 (G), SR2.3 (QD)
ROWPGATE7: R14.1, ROW7..4 (G), SR2.5 (QF)
SCK: JP1.6, SR1.11 (SCK), SR2.11 (SCK), SR3.11 (SCK), SR4.11 (SCK), SR5.11 (SCK), SR6.11 (SCK), SR7.11 (SCK), SR8.11 (SCK), SR9.11 (SCK), SR10.11 (SCK), SR11.11 (SCK), SR12.11 (SCK), SR13.11 (SCK)
SR1TOSR2: SR1.9 (QH*), SR2.14 (SER)
SR2TOSR3: SR2.9 (QH*), SR3.14 (SER)
SR3TOSR4: SR3.9 (QH*), SR4.14 (SER)
SR4TOSR5: SR4.9 (QH*), SR5.14 (SER)
SR5TOSR6: SR5.9 (QH*), SR6.14 (SER)
SR6TOSR7: SR6.9 (QH*), SR7.14 (SER)
SR7TOSR8: SR7.9 (QH*), SR8.14 (SER)
SR8TOSR9: SR8.9 (QH*), SR9.14 (SER)
SR9TOSR10: SR9.9 (QH*), SR10.14 (SER)
SR10TOSR11: SR10.9 (QH*), SR11.14 (SER)
SR11TOSR12: SR11.9 (QH*), SR12.14 (SER)
SR12TOSR13: SR12.9 (QH*), SR13.14 (SER)
VCC: C1.1, C2.1, C3.1, C4.1, C5.1, C6.1, C7.1, C8.1, C9.1, C10.1, C11.1, C12.1, C13.1, JP1.2, LOGICCAP.+, SR1.10 (SCL), SR1.16 (VCC), SR2.10 (SCL), SR2.16 (VCC), SR3.10 (SCL), SR3.16 (VCC), SR4.10 (SCL), SR4.16 (VCC), SR5.10 (SCL), SR5.16 (VCC), SR6.10 (SCL), SR6.16 (VCC), SR7.10 (SCL), SR7.16 (VCC), SR8.10 (SCL), SR8.16 (VCC), SR9.10 (SCL), SR9.16 (VCC), SR10.10 (SCL), SR10.16 (VCC), SR11.10 (SCL), SR11.16 (VCC), SR12.10 (SCL), SR12.16 (VCC), SR13.10 (SCL), SR13.16 (VCC)

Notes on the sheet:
For all PN MOSFETs (Rows and Cols) -------------------------------------------- Lower numbered (name) resistor goes on lower section of ea group of PN MOSFETs. P is top MOS, N is bottom MOS.
logic vcc

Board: 4 copper layers, 97 parts (0 on the bottom side), 182 nets, no tracks yet.

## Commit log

2015-12-27 :boom::camel: Added .gitattributes & .gitignore files
2015-12-27 Initial Seed Commit. (Rev 1)
    This is the first hardware revision of my 45x7 flip dot controller
    board. This has been sent to fab and works with a Luminator MAX3000 45x7
    side sign single panel.
2015-12-27 Initial HW Rev2 commit.
    This Rev is a work in progress and is not ready to be sent to fab.
2015-12-27 Add bill of materials needed to produce PCB
